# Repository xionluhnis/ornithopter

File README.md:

# Ornithopter with ATMega328p
Ornithopter board, code and more for HTMAA.

* Generic board using ATMega328p with [avrdude](http://savannah.nongnu.org/projects/avrdude) for programming
* Initial control code for wing flapping using two servo motors
* Communication using nRF24 and the [RF24](http://tmrh20.github.io/RF24/) library, slightly modified to work without requiring the Arduino code

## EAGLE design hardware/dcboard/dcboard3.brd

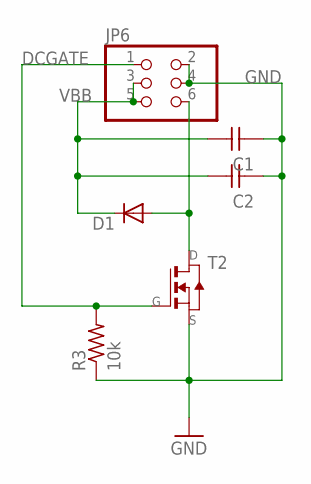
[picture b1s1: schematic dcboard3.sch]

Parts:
C1, C2: CAP-UNPOLARIZEDFAB; C1206FAB
D1: DIODESOD123; SOD123
JP6: PINHD-2X3-SMD; 2X03SMD
R3: 10k; R1206FAB
T2: NMOSFETTO252; TO252

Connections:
DCGATE: JP6.1, R3.2, T2.1 (G)
GND: C1.1, C2.1, JP6.2, JP6.4, R3.1, T2.2 (S)
unnamed: D1.ANODE (A), JP6.6, T2.3 (D)
VBB: C1.2, C2.2, D1.CATHODE (C), JP6.3, JP6.5

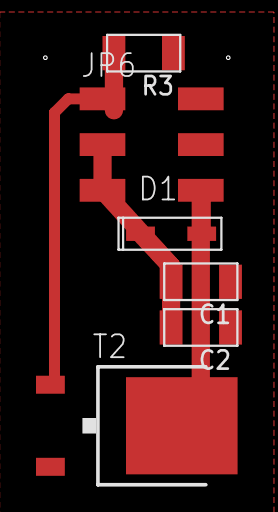
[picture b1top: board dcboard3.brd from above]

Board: 2 copper layers, 6 parts (0 on the bottom side), 4 nets.

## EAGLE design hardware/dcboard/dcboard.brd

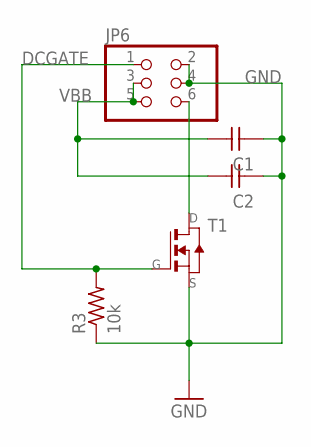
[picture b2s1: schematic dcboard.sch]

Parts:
C1, C2: CAP-UNPOLARIZEDFAB; C1206FAB
JP6: PINHD-2X3-SMD; 2X03SMD
R3: 10k; R1206FAB
T1: NMOSFETSOT23; SOT-23

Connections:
DCGATE: JP6.1, R3.2, T1.3 (G)
GND: C1.1, C2.1, JP6.2, JP6.4, R3.1, T1.2 (S)
unnamed: JP6.6, T1.1 (D)
VBB: C1.2, C2.2, JP6.3, JP6.5

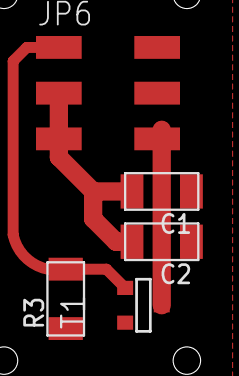
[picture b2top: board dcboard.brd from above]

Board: 2 copper layers, 5 parts (0 on the bottom side), 4 nets.

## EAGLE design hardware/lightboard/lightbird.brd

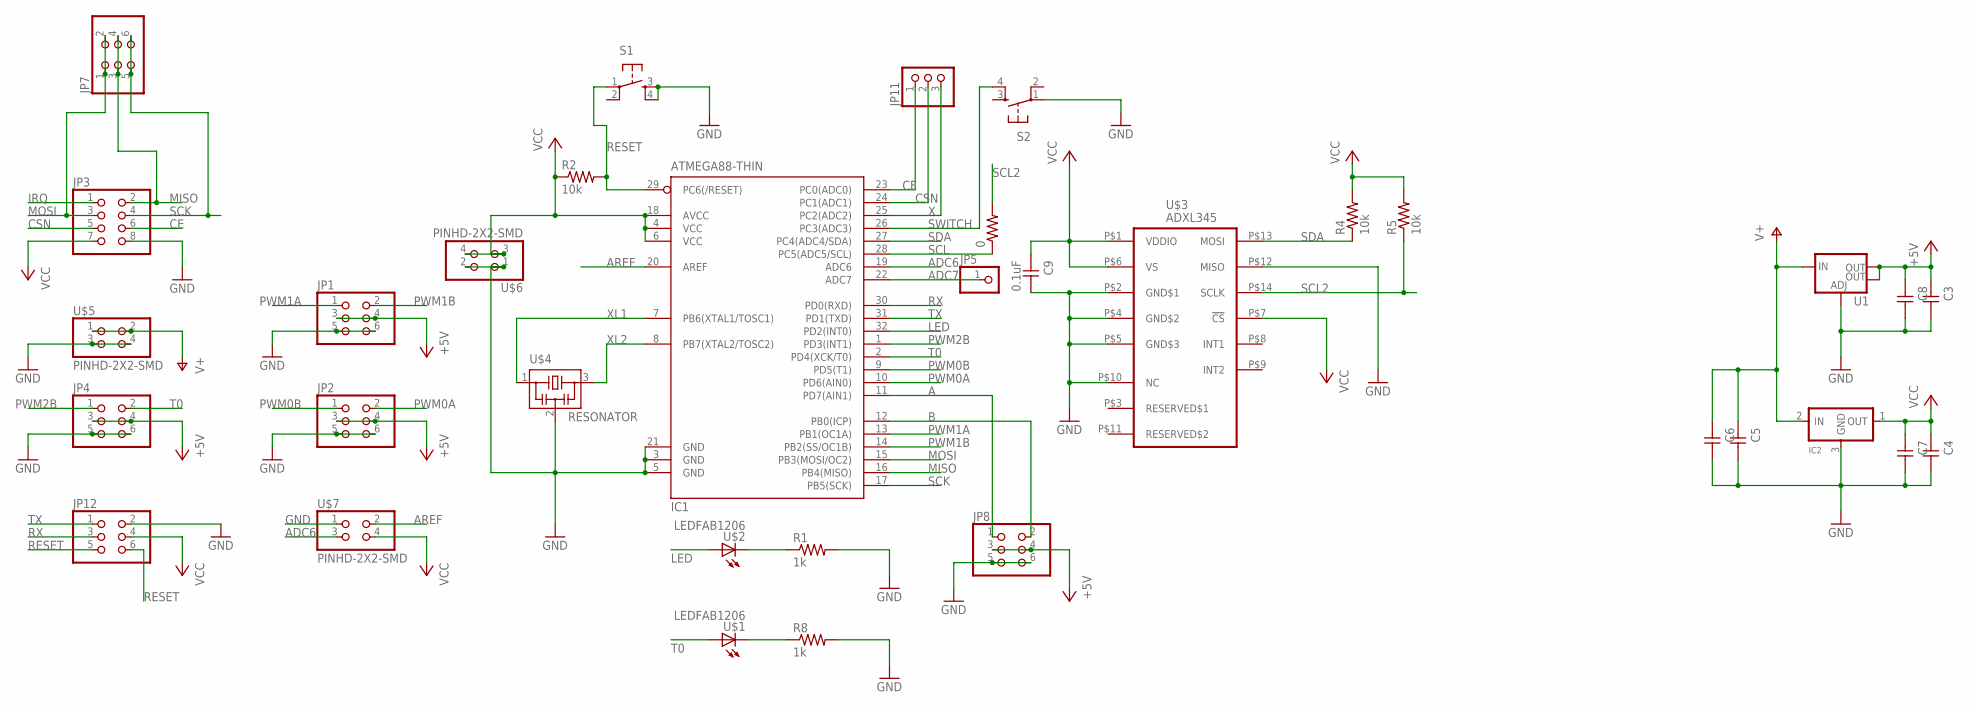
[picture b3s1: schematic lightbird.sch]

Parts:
0: RES-US1206FAB; R1206FAB
C3, C4, C5, C6, C7, C8: CAP-UNPOLARIZEDFAB; C1206FAB
C9: 0.1uF; C1206FAB
IC1: ATMEGA88-THIN; TQFP32-08THIN
IC2: REGULATORSOT23; SOT23
JP1, JP2, JP4, JP7, JP8, JP12: PINHD-2X3-SMD; 2X03SMD
JP3: PINHD-2X4SMT; 2X04_SMT
JP5: PINHD-1X1; 1X01
JP11: PINHD-1X3; 1X03
R1, R8: 1k; R1206FAB
R2, R4, R5: 10k; R1206FAB
S1, S2: 6MM_SWITCH6MM_SWITCH; 6MM_SWITCH
U1: V_REG_LM1117SOT223; SOT223
U$1, U$2: LEDFAB1206; LED1206FAB
U$3: ADXL345; LGA14
U$4: RESONATOR; EFOBM
U$5, U$6, U$7: PINHD-2X2-SMD; 2X02SMD

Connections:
+5V: C3.1, C8.1, JP1.3, JP1.4, JP2.3, JP2.4, JP4.3, JP4.4, JP8.3, JP8.4, U1.2 (OUT), U1.4 (OUT)
A: IC1.11 (PD7(AIN1)), JP8.1
ADC6: IC1.19 (ADC6), U$7.3
ADC7: IC1.22 (ADC7), JP5.1
AREF: IC1.20 (AREF), U$7.2
B: IC1.12 (PB0(ICP)), JP8.2
CE: IC1.23 (PC0(ADC0)), JP3.6, JP11.1
CSN: IC1.24 (PC1(ADC1)), JP3.5, JP11.2
GND: C3.2, C4.2, C5.2, C6.2, C7.2, C8.2, C9.2, IC1.3 (GND), IC1.5 (GND), IC1.21 (GND), IC2.3 (GND), JP1.5, JP1.6, JP2.5, JP2.6, JP3.8, JP4.5, JP4.6, JP8.5, JP8.6, JP12.2, R1.2, R8.2, S1.3 (S), S1.4 (S1), S2.1, U1.1 (ADJ), U$3.P$2 (GND$1), U$3.P$4 (GND$2), U$3.P$5 (GND$3), U$3.P$10 (NC), U$3.P$12 (MISO), U$4.2, U$5.3, U$5.4, U$6.1, U$6.2, U$7.1
IRQ: JP3.1
LED: IC1.32 (PD2(INT0)), U$2.1 (A)
MISO: IC1.16 (PB4(MISO)), JP3.2, JP7.3, JP7.4
MOSI: IC1.15 (PB3(MOSI/OC2)), JP3.3, JP7.1, JP7.2
unnamed: R1.1, U$2.2 (C)
unnamed: R8.1, U$1.2 (C)
PWM0A: IC1.10 (PD6(AIN0)), JP2.2
PWM0B: IC1.9 (PD5(T1)), JP2.1
PWM1A: IC1.13 (PB1(OC1A)), JP1.1
PWM1B: IC1.14 (PB2(SS/OC1B)), JP1.2
PWM2B: IC1.1 (PD3(INT1)), JP4.1
RESET: IC1.29 (PC6(/RESET)), JP12.5, JP12.6, R2.2, S1.1
RX: IC1.30 (PD0(RXD)), JP12.3
SCK: IC1.17 (PB5(SCK)), JP3.4, JP7.5, JP7.6
SCL: 0.1, IC1.28 (PC5(ADC5/SCL))
SCL2: 0.2, R5.1, U$3.P$14 (SCLK)
SDA: IC1.27 (PC4(ADC4/SDA)), R4.1, U$3.P$13 (MOSI)
SWITCH: IC1.26 (PC3(ADC3)), S2.4 (S1)
T0: IC1.2 (PD4(XCK/T0)), JP4.2, U$1.1 (A)
TX: IC1.31 (PD1(TXD)), JP12.1
V+: C5.1, C6.1, IC2.2 (IN), U1.3 (IN), U$5.1, U$5.2
VCC: C4.1, C7.1, C9.1, IC1.4 (VCC), IC1.6 (VCC), IC1.18 (AVCC), IC2.1 (OUT), JP3.7, JP12.4, R2.1, R4.2, R5.2, U$3.P$1 (VDDIO), U$3.P$6 (VS), U$3.P$7 (!CS), U$6.3, U$6.4, U$7.4
X: IC1.25 (PC2(ADC2)), JP11.3
XL1: IC1.7 (PB6(XTAL1/TOSC1)), U$4.1
XL2: IC1.8 (PB7(XTAL2/TOSC2)), U$4.3

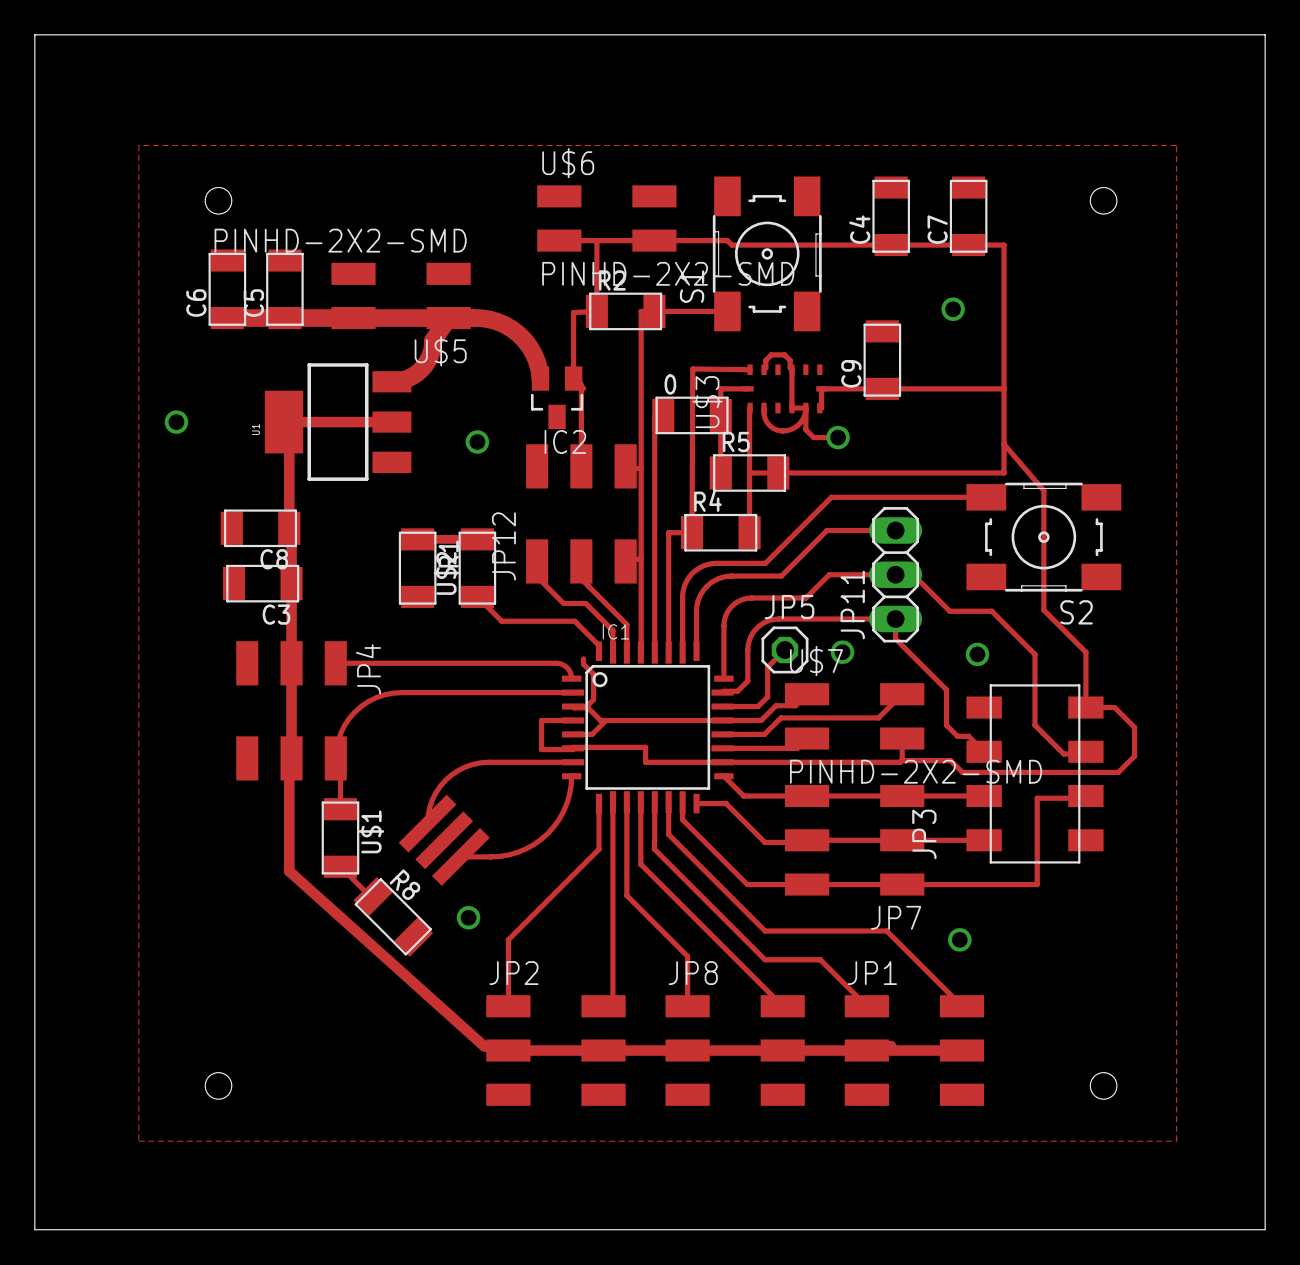
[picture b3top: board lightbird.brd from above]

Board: 2 copper layers, 70.6 x 68.6 mm, 34 parts (0 on the bottom side), 33 nets.

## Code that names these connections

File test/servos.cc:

// Alexandre Kaspar <akaspar@mit.edu>

#include <avr/io.h>
#include <util/delay.h>
#include <stdint.h>

void toggle_led(){
  static char state = 0;
  DDRD |= (1 << PD2);
  if(state)
    PORTD |= (1 << PD2);
  else
    PORTD &= ~(1 << PD2);
  state = !state;
}

int main(void) {

    // set clock divider to /1
    // @see https://www.avrprogrammers.com/howto/sysclk-prescaler
    CLKPR = (1 << CLKPCE);
    CLKPR = (0 << CLKPS3) | (0 << CLKPS2) | (0 << CLKPS1) | (0 << CLKPS0);
    
    // PWM setup on 16-bit counter
    TCCR1A = (1 << COM1A1) | (0 << COM1A0) | (1 << COM1B1) | (0 << COM1B0); // clear OC1A/B on compare match
    TCCR1B = (0 << CS12) | (1 << CS11) | (0 << CS10) | (1 << WGM13); // prescaler /8, phase and frequency correct PWM, ICR1 TOP
    ICR1 = 25000; // 20 ms frequency
    DDRB |= (1 << PB1) | (1 << PB2);

    // PWM setup on 8-bit counter 0 (B)
    TCCR0A = (1 << COM0A1) | (0 << COM0A0) | (1 << COM0B1) | (0 << COM0B0) | (1 << WGM00);
    TCCR0B = (1 << CS02) | (0 << CS01) | (1 << CS00) | (1 << WGM02); // prescaler /1024, phase correct PWM, OCRA TOP
    OCR0A = 195; // 20MHz / 1024 / 2 / 195 = 50.08 Hz
    DDRD |= (1 << PD5) | (1 << PD6);

    // PWM setup on 8-bit counter 2 (B)
    TCCR2A = (1 << COM2B1) | (0 << COM2B0) | (1 << WGM20);
    TCCR2B = (1 << CS02) | (1 << CS01) | (1 << CS00) | (1 << WGM22); // prescaler /1024, phase correct PWM, OCRA TOP
    OCR2A = 195; // 20MHz / 1024 / 2 / 195 = 50.08 Hz
    DDRD |= (1 << PD3);

    // LOOP
    while(1){
    
        OCR1A = 1250;
        OCR1B = 1250;
        OCR0B = 10;
        OCR2B = 10;
        _delay_ms(1000);
        OCR1A = 1875;
        OCR1B = 1875;
        OCR0B = 15;
        OCR2B = 15;
        _delay_ms(1000);
        OCR1A = 2500;
        OCR1B = 2500;
        OCR0B = 20;
        OCR2B = 20;
        _delay_ms(1000);

        toggle_led();
    }
    
    return 0;
}

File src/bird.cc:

// Alexandre Kaspar <akaspar@mit.edu>

#include <avr/io.h>
#include <util/delay.h>
#include <stdint.h>

// angle definition for wings
#ifndef TOP_ANGLE
#define TOP_ANGLE 40
#endif
#ifndef BOT_ANGLE
#define BOT_ANGLE 20
#endif
// PWM conversion
// 90deg  = 1ms   = 1250
// 0deg   = 1.5ms = 1875
// -90deg = 2ms   = 2500
#define PWM_MAX 2500UL
#define PWM_MID 1875UL
#define PWM_MIN 1250UL
// our angles
#define PWM_TOP (PWM_MID + (PWM_MAX - PWM_MID) * TOP_ANGLE / 90UL)
#define PWM_BOT (PWM_MID - (PWM_MID - PWM_MIN) * BOT_ANGLE / 90UL)
#define PWM_INV(a) (PWM_MIN + PWM_MAX - a)

// maximum allowed consecutive timeouts before going into landing
#ifndef MAX_TIMEOUTS
#define MAX_TIMEOUTS -1
#endif
// timeout in milliseconds
#ifndef RADIO_TIMEOUT
#define RADIO_TIMEOUT 100
#endif
// radio poll every so often (milliseconds)
#ifndef RADIO_POLLING_PERIOD
#define RADIO_POLLING_PERIOD 1000 
#endif

#ifndef WIRED

// control from serial board
#define RADIO_NUM 1
#include "radio.h"

#endif

#include "command.h"
#include "control.h"
#include "pwm.h"
#include "time.h"
#include "usart.h"

void toggle_led(){
  static char state = 0;
  DDRD |= (1 << PD2);
  if(state)
    PORTD |= (1 << PD2);
  else
    PORTD &= ~(1 << PD2);
  state = !state;
}

// global variables
Control controller;
unsigned long maxFrequency = 10UL; // 10 toggles per second
bool running = false;
// counters / timers
unsigned long counter = 0;
uint8_t numTimeouts = 0;

bool check_run_switch();
void update_wings();
void update_tail();
void radio_input();

int main(void) {

  clock_init(); // /1 prescaler
#ifdef WIRED
  USART_init();
  USART_send("Bird initializing.\r\n");
#else
  radio_init();
#endif
  pwm0_init();
  pwm1_init();
  pwm2_init();
  // and finally the time system
  time_init();

  // switch => pullup
  PORTC |= (1 << PC3);
  DDRD |= (1 << PD7); // trigger signal

#ifdef WIRED
  USART_send("\r\nDDRB=");
  USART_sendNumber(DDRB, 2);
  USART_send("\r\nDDRC=");
  USART_sendNumber(DDRC, 2);
  USART_send("\r\nDDRD=");
  USART_sendNumber(DDRD, 2);
  USART_send("\r\n\r\nPORTB=");
  USART_sendNumber(PORTB, 2);
  USART_send("\r\nPORTC=");
  USART_sendNumber(PORTC, 2);
  USART_send("\r\nPORTD=");
  USART_sendNumber(PORTD, 2);
  USART_send("\r\n");
#endif

  // LOOP
  while(1){
    // USART_sendNumber(millis());
    // USART_send("\r\n");

    // switches
    if(check_run_switch())
      running = !running;

    // update speed
    update_wings();

    // update orientation
    update_tail();

#ifdef WIRED
    if(USART_ready_to_read()){
      unsigned char c = USART_read();
      USART_send("Input: ");
      USART_send(c);
      USART_send("\r\n");
      Command cmd = 0;
      if(controller.input(c, &cmd)){
        USART_send("Command: ");
        USART_sendNumber(cmd, 16);
        USART_send("\r\n");
      }
    }

#else
    radio_input();
#endif

    toggle_led();
    ++counter;

#ifdef WIRED
    if(counter % 10000 == 0){
      USART_send("m=");
      USART_sendNumber(millis());
      USART_send("\r\n");
    }
#endif

    // second led
    if(seconds() % 2)
      PORTD |= (1 << PD4);
    else
      PORTD &= ~(1 << PD4);
  }
  
  return 0;
}


bool check_run_switch(){
  static unsigned long lastSwitch = 0;
  bool trigger = false;
  bool runSwitch = PINC & (1 << PC3); // is the switch being pressed?
  if(!runSwitch){
    unsigned long now = millis();
    trigger = now > lastSwitch + 1000UL;
    lastSwitch = now; // so we can press as long as we want (and only count after release)
  }
  return trigger;
}

void update_wings(){
  static unsigned long lastToggle = 0;
  static enum {
    TOP,
    MIDDLE,
    BOTTOM
  } wingState = MIDDLE;
  // cases
  if(!running || (MAX_TIMEOUTS >= 0 && numTimeouts > MAX_TIMEOUTS)){
    // if not active, stay in mid position
    wingState = MIDDLE;
    OCR1A = PWM_MID;
    OCR1B = PWM_MID;
  } else if(!controller.speed){
    // special case, we go at the top angle
    wingState = TOP;
    OCR1A = PWM_TOP;
    OCR1B = PWM_BOT;
  } else {
    unsigned long now = millis();
    // full speed (100) => 10Hz toggle cycle (1 up + 1 down)
    unsigned long deltaThreshold = 1000UL * maxFrequency / ((unsigned long)controller.speed) / 2UL;
    // Note: / 2 is because we need two toggles (1 up + 1 down)
    if(now  >= lastToggle + deltaThreshold){
      if(wingState == TOP)
        wingState = BOTTOM;
      else
        wingState = TOP;
      lastToggle = now;
      // change PWM
      if(wingState == BOTTOM) {
        OCR1A = PWM_BOT;
        OCR1B = PWM_TOP;
      } else {
        OCR1A = PWM_TOP;
        OCR1B = PWM_BOT;
      }
    }
  }
}

void update_tail(){
  // TODO implement this!
}

void radio_input(){
  static unsigned long lastRadio = 0;
  unsigned long now = millis();

  // only poll every so often
  // TODO the polling should depend on speed
  // TODO communication should be done with interrupts, not
  if(now < lastRadio + RADIO_POLLING_PERIOD)
    return;
  else
    lastRadio = now;

  // process input from user
  bool timeout = false;
  while ( ! radio.available() ){
    if(millis() > now + RADIO_TIMEOUT){
      timeout = true;
      break;
    }
  }
  if ( timeout ){
#if MAX_TIMEOUTS == -1
    return; // we just skip this time
#endif
    // If it times out too many times, we stop the bird by precaution
    // Note: do not let count overflow (else the bird may be in an odd state)
    if(numTimeouts < 255)
      ++numTimeouts;
  }else{
    // reset timeout counter
    numTimeouts = 0;

    // get radio command
    Command response = 0;
    radio.read( &response, sizeof(Command) );

    CommandType what = get_type(response);
    union {
      uint8_t u;
      int8_t  s;
    } data;
    data.u = get_data(response);
    switch(what){

      case Stop:
        if(data.u == 0xFE)
          controller.reset();
        else
          controller.stop();
        break;

      case SetDirection:
        controller.direction = data.s;
        break;

      case SetSpeed:
        controller.speed = data.u;
        break;

      case Trigger:
        // different types of triggers
        switch(data.u){
          case 0x00:
            running = !running;
            break;
          
          case 0x01: {
              static bool triggered = false;
              triggered = !triggered;
              if(triggered)
                PORTD |= (1 << PD7);
              else
                PORTD &= ~(1 << PD7);
            } break;

          default:
            break;
        }
        break;

      default:
#ifdef WIRED
        // this actualy never gets reached right now
        USART_send("Unsupported command: ");
        USART_sendNumber(static_cast<uint8_t>(what), 16);
        USART_send("\r\n");
#endif
        break;
    }
  }

}

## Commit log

2017-12-09 Added libraries and board files: - Eagle files and SRM20 pngs for Mods - Arduino cores and libs sources - DigitalIO for software IO - RF24 for communicating over nRF24
2017-12-09 Hello world example
2017-12-09 Added led example to debug timing and fuses, changed Makefile to be more generic
2017-12-10 Working helloworld and new echo example
2017-12-10 Wing servo example
2017-12-10 WIP servos with counter0
2017-12-10 Working third servo
2017-12-10 Added 4th working servo
2017-12-10 Cleaned servo example (no need for serial here)
2017-12-10 Base of accelerometer test
2017-12-11 Working accelerator example
2017-12-11 Accelerometer example output for web UI
2017-12-11 New nRF24 example working
2017-12-11 DC motor example
2017-12-11 Better frequency for dc motor
2017-12-12 More reasonable wait time for LED
2017-12-12 New RADIO_CE and RADIO_CSN variables in makefile and radio.cc
2017-12-13 Remove DigialIO since we don't need software implementations, updated bird board to newer version
2017-12-13 New boards
2017-12-13 Traces for dcboard
2017-12-15 New car and serial code
2017-12-15 WIP serial and car
2017-12-15 Basic serial logic
2017-12-16 Slightly more verbose
2017-12-16 New dcboard with bigger mosfet
2017-12-16 New dcboard with flyback diode
2017-12-17 WIP bird
2017-12-17 New time management, new control and serial reformatting, basic bird with wing flapping mechanism
2017-12-17 New bird logic, PWM working, but flapping buggy
2017-12-17 Working wing flapping
2017-12-19 New bird code to use RF input, and treating timeouts with milliseconds now
2017-12-19 New trigger command
2017-12-20 New timeout treatments
